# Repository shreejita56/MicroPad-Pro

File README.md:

# MicroPad-Pro

So I made a custom 3X3 micropad with three rotor encoder that controls Brightness, Volume , scroll . The Micropad is based on Arduino Pro-Micro and each switch has a diode connected to it to prevent ghosting. The micropad is mainly designed for Normal day short Cuts . PCB was designed on kicad and 3D model was made in fusion 360
### Features
- Based on Arduino Pro-Micro
- has a compact design
- has diode to protect ghosting
- 3x3 Switch Matrix and 3 Rotor to control Volume ,  Brightness ,scroll

  ## BOM

| Item | Price (USD) | Source |
|---|---:|---|
| PCB + 3D Print + Shipping (Coupons Applied) | $15.72 | JLCPCB |
| Arduino Pro-Micro + Shipping | $5.30 | [Robocraze](https://robocraze.com/products/seeed-studio-xiao-rp2040-development-board?variant=47742255562976&country=IN&currency=INR) |
| Keycaps (Pack of 5 × 2) | $1.05 | [Meckeys](https://meckeys.com/shop/accessories/keyboard-accessories/keycaps/blank/blank-dsa-keycaps-1u/?attribute_pa_variations=off-white) |
| Meckeys Shipping | $1.10 | [Meckeys](https://meckeys.com/) |
| Diodes (10 Pieces) | Already Owned | [Indian Hobby Center](https://www.indianhobbycenter.com/products/zener-diode-1n4148) |
| Rotary Encoder | Already Owned | [Robu.in](https://robu.in/product/green-rotary-encoder-module-for-arduino-without-demo-code/) |
| **Total** | **$23.17** | |

  ## Schematics

  ## PCB

  ## CAD

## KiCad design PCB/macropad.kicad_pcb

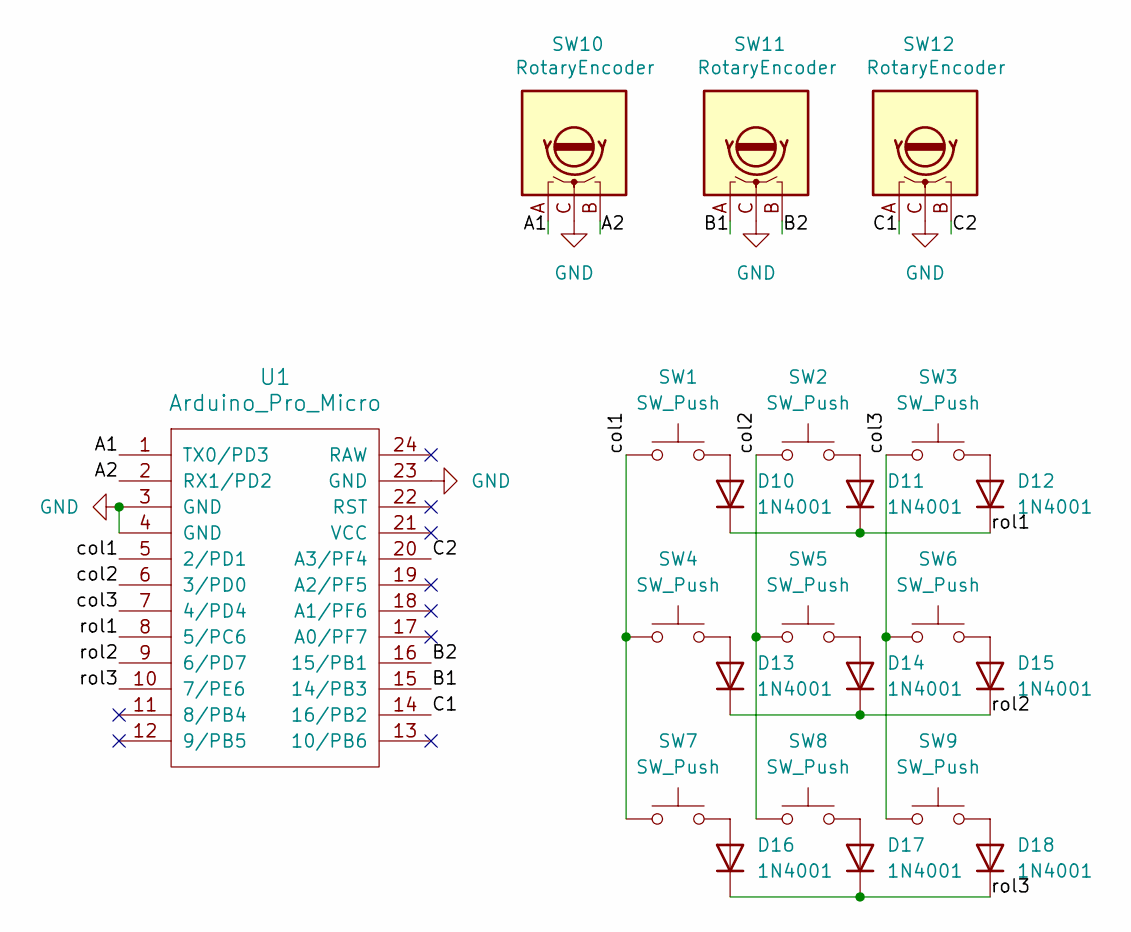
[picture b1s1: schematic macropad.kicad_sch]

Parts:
D10, D11, D12, D13, D14, D15, D16, D17, D18: 1N4001; D_DO-41_SOD81_P10.16mm_Horizontal
SW1, SW2, SW3, SW4, SW5, SW6, SW7, SW8, SW9: SW_Push; SW_Cherry_MX_1.00u_PCB
SW10, SW11, SW12: RotaryEncoder; RotaryEncoder_Alps_EC11E_Vertical_H20mm
U1: Arduino_Pro_Micro

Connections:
/A1: SW10.A, U1.1 (TX0/PD3)
/A2: SW10.B, U1.2 (RX1/PD2)
/B1: SW11.A, U1.15 (14/PB3)
/B2: SW11.B, U1.16 (15/PB1)
/C1: SW12.A, U1.14 (16/PB2)
/C2: SW12.B, U1.20 (A3/PF4)
/col1: SW1.1, SW4.1, SW7.1, U1.5 (2/PD1)
/col2: SW2.1, SW5.1, SW8.1, U1.6 (3/PD0)
/col3: SW3.1, SW6.1, SW9.1, U1.7 (4/PD4)
/rol1: D10.1 (K), D11.1 (K), D12.1 (K), U1.8 (5/PC6)
/rol2: D13.1 (K), D14.1 (K), D15.1 (K), U1.9 (6/PD7)
/rol3: D16.1 (K), D17.1 (K), D18.1 (K), U1.10 (7/PE6)
GND: SW10.C, SW11.C, SW12.C, U1.3 (GND), U1.4 (GND), U1.23 (GND)
unnamed: D10.2 (A), SW1.2
unnamed: D11.2 (A), SW2.2
unnamed: D12.2 (A), SW3.2
unnamed: D13.2 (A), SW4.2
unnamed: D14.2 (A), SW5.2
unnamed: D15.2 (A), SW6.2
unnamed: D16.2 (A), SW7.2
unnamed: D17.2 (A), SW8.2
unnamed: D18.2 (A), SW9.2

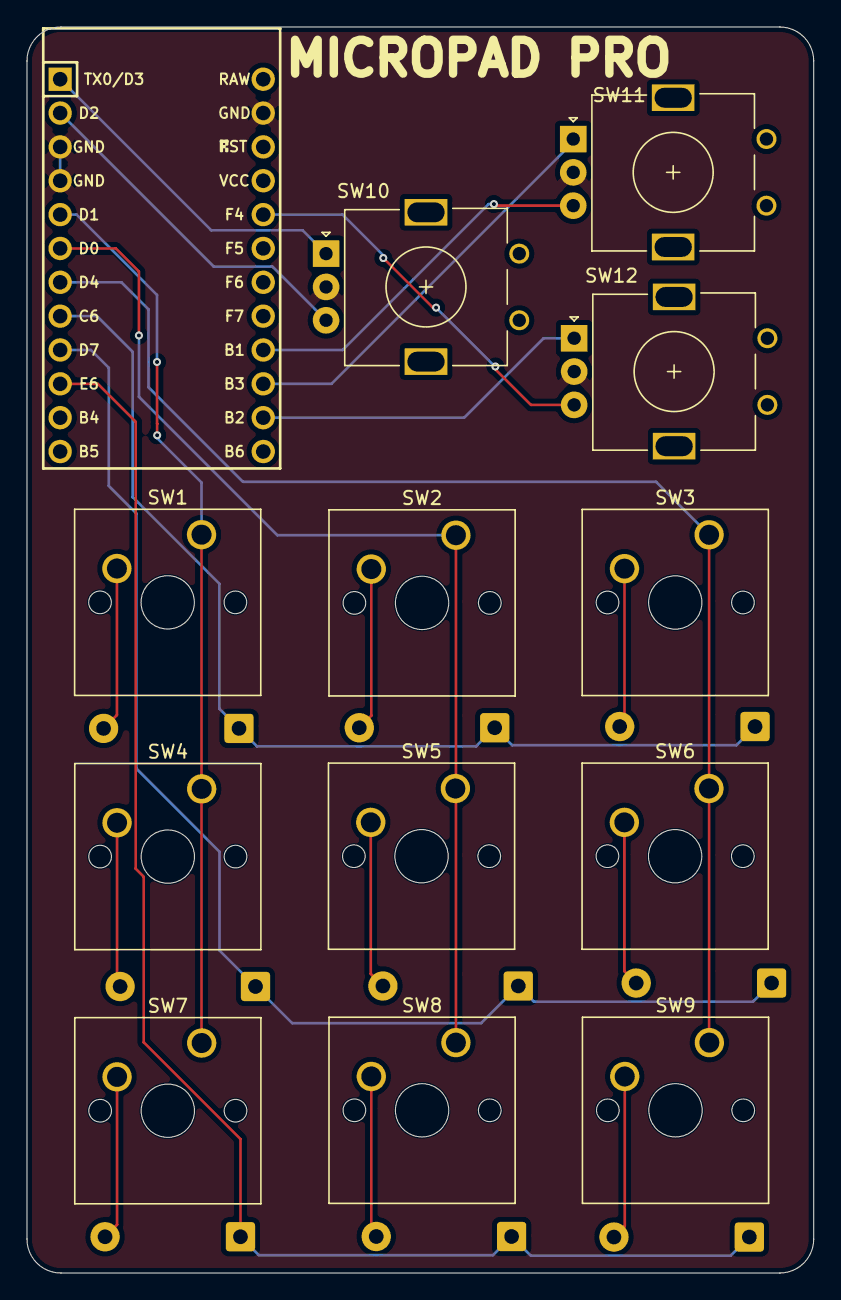
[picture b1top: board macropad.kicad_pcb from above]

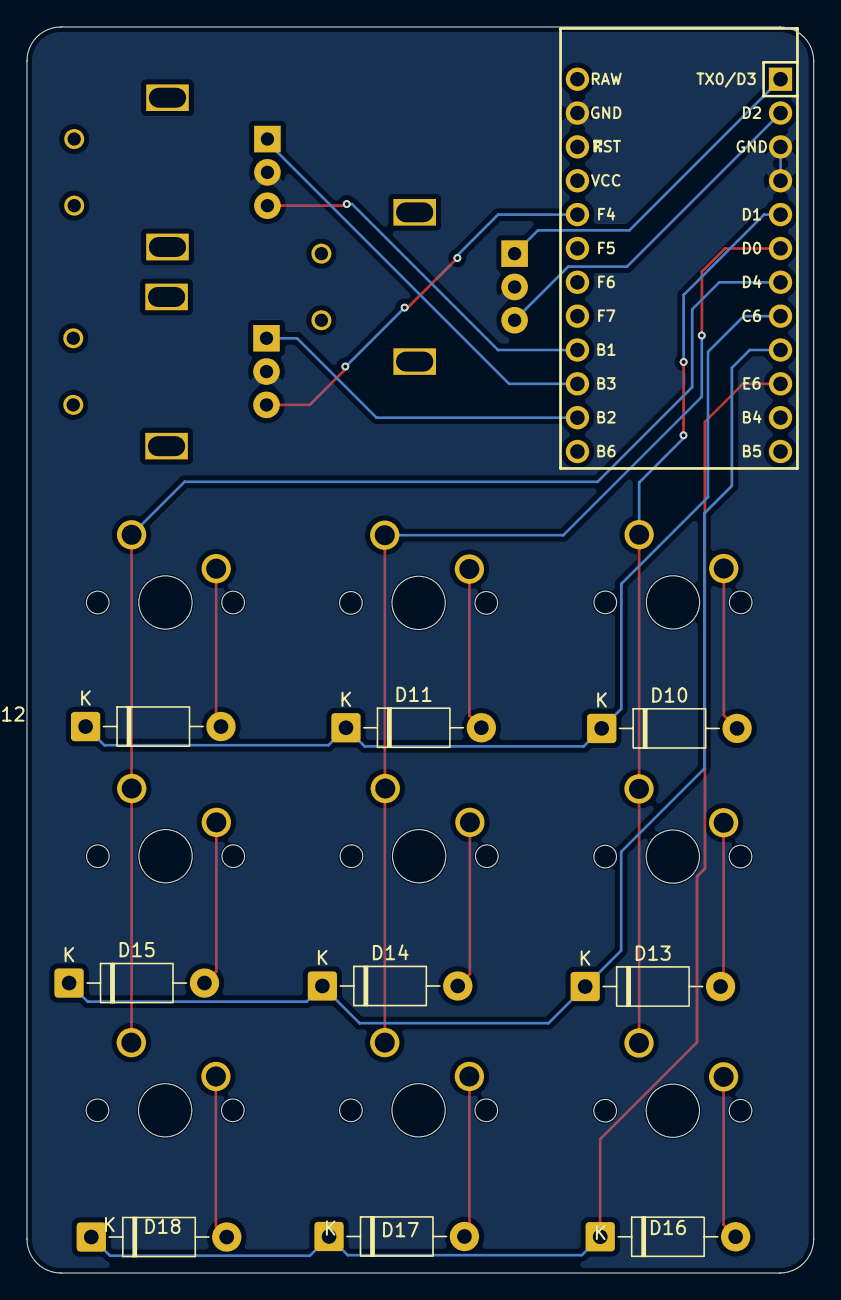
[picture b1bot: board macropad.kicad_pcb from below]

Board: 2 copper layers, 59.0 x 93.5 mm, 22 parts (9 on the bottom side), 22 nets.
